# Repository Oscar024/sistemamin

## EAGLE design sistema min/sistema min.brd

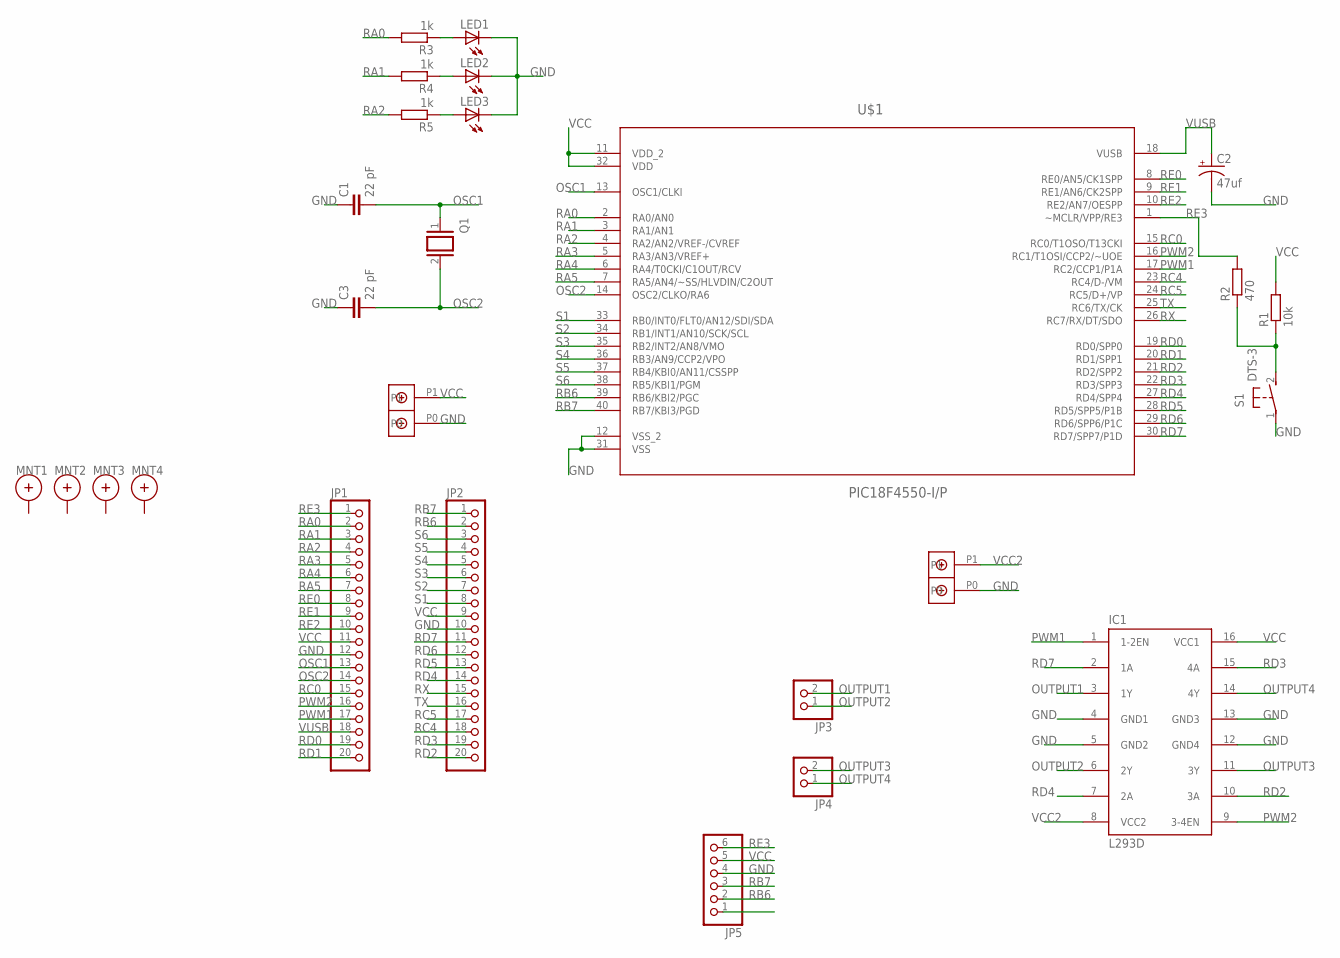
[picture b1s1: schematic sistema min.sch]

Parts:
C1, C3: 22 pF; C050-025X075
C2: 47uf; E5-10,5
IC1: L293D; DIL16
JP1, JP2: PINHD-1X20; 1X20
JP3, JP4: PINHD-1X2; 1X02
JP5: PINHD-1X6; 1X06
LED1, LED2, LED3: LED3MM
MNT1, MNT2, MNT3, MNT4: HOLE_MNT_0.135; HOLE_MNT_#5-40
Q1: XTAL/S; QS
R1: 10k; 0204/7
R2: 470; 0204/7
R3, R4, R5: 1k; 0204/7
S1: DTS-3
U$1: PIC18F4550-I/P; DIP254P1524X635-40
U$2, U$3: DBCONN-1X2

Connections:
GND: C1.1, C2.-, C3.1, IC1.4 (GND1), IC1.5 (GND2), IC1.12 (GND4), IC1.13 (GND3), JP1.12, JP2.10, JP5.4, LED1.K (C), LED2.K (C), LED3.K (C), S1.1, U$1.12 (VSS_2), U$1.31 (VSS), U$2.P0, U$3.P0
unnamed: R1.1, R2.1, S1.2
unnamed: LED1.A, R3.1
unnamed: LED2.A, R4.1
unnamed: LED3.A, R5.1
OSC1: C1.2, JP1.13, Q1.1, U$1.13 (OSC1/CLKI)
OSC2: C3.2, JP1.14, Q1.2, U$1.14 (OSC2/CLKO/RA6)
OUTPUT1: IC1.3 (1Y), JP3.2
OUTPUT2: IC1.6 (2Y), JP3.1
OUTPUT3: IC1.11 (3Y), JP4.2
OUTPUT4: IC1.14 (4Y), JP4.1
PWM1: IC1.1 (1-2EN), JP1.17, U$1.17 (RC2/CCP1/P1A)
PWM2: IC1.9 (3-4EN), JP1.16, U$1.16 (RC1/T1OSI/CCP2/~UOE)
RA0: JP1.2, R3.2, U$1.2 (RA0/AN0)
RA1: JP1.3, R4.2, U$1.3 (RA1/AN1)
RA2: JP1.4, R5.2, U$1.4 (RA2/AN2/VREF-/CVREF)
RA3: JP1.5, U$1.5 (RA3/AN3/VREF+)
RA4: JP1.6, U$1.6 (RA4/T0CKI/C1OUT/RCV)
RA5: JP1.7, U$1.7 (RA5/AN4/~SS/HLVDIN/C2OUT)
RB6: JP2.2, JP5.2, U$1.39 (RB6/KBI2/PGC)
RB7: JP2.1, JP5.3, U$1.40 (RB7/KBI3/PGD)
RC0: JP1.15, U$1.15 (RC0/T1OSO/T13CKI)
RC4: JP2.18, U$1.23 (RC4/D-/VM)
RC5: JP2.17, U$1.24 (RC5/D+/VP)
RD0: JP1.19, U$1.19 (RD0/SPP0)
RD1: JP1.20, U$1.20 (RD1/SPP1)
RD2: IC1.10 (3A), JP2.20, U$1.21 (RD2/SPP2)
RD3: IC1.15 (4A), JP2.19, U$1.22 (RD3/SPP3)
RD4: IC1.7 (2A), JP2.14, U$1.27 (RD4/SPP4)
RD5: JP2.13, U$1.28 (RD5/SPP5/P1B)
RD6: JP2.12, U$1.29 (RD6/SPP6/P1C)
RD7: IC1.2 (1A), JP2.11, U$1.30 (RD7/SPP7/P1D)
RE0: JP1.8, U$1.8 (RE0/AN5/CK1SPP)
RE1: JP1.9, U$1.9 (RE1/AN6/CK2SPP)
RE2: JP1.10, U$1.10 (RE2/AN7/OESPP)
RE3: JP1.1, JP5.6, R2.2, U$1.1 (~MCLR/VPP/RE3)
RX: JP2.15, U$1.26 (RC7/RX/DT/SDO)
S1: JP2.8, U$1.33 (RB0/INT0/FLT0/AN12/SDI/SDA)
S2: JP2.7, U$1.34 (RB1/INT1/AN10/SCK/SCL)
S3: JP2.6, U$1.35 (RB2/INT2/AN8/VMO)
S4: JP2.5, U$1.36 (RB3/AN9/CCP2/VPO)
S5: JP2.4, U$1.37 (RB4/KBI0/AN11/CSSPP)
S6: JP2.3, U$1.38 (RB5/KBI1/PGM)
TX: JP2.16, U$1.25 (RC6/TX/CK)
VCC: IC1.16 (VCC1), JP1.11, JP2.9, JP5.5, R1.2, U$1.11 (VDD_2), U$1.32 (VDD), U$2.P1
VCC2: IC1.8 (VCC2), U$3.P1
VUSB: C2.+, JP1.18, U$1.18 (VUSB)

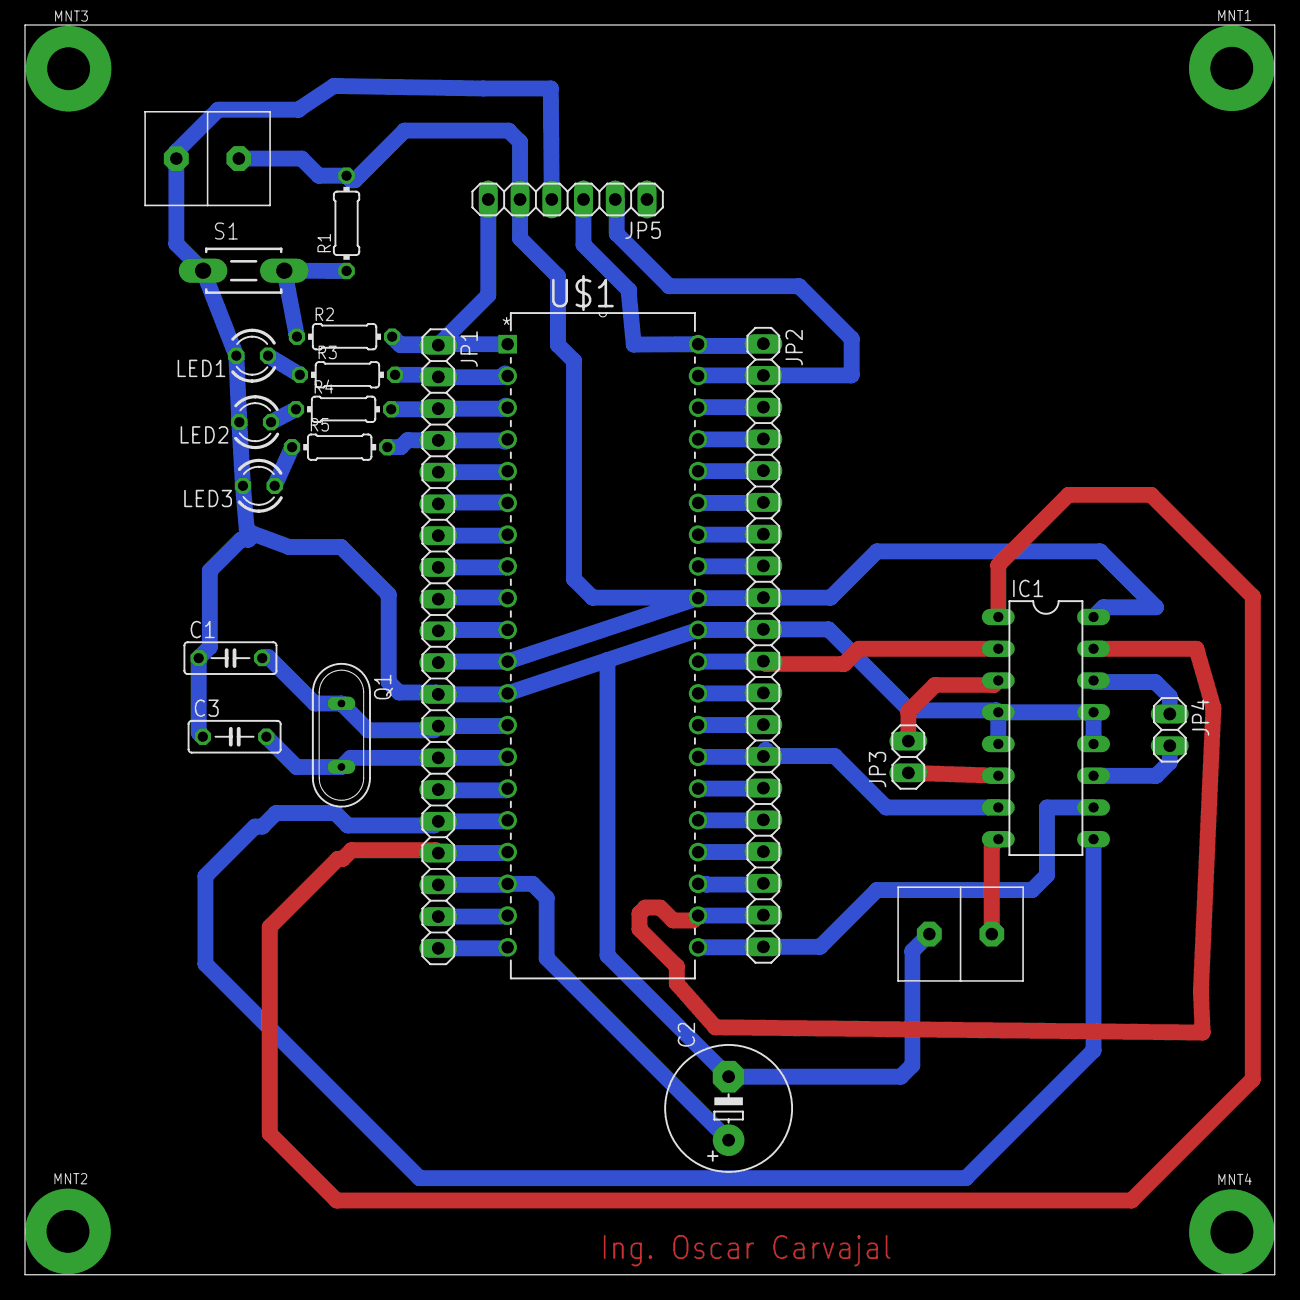
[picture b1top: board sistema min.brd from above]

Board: 2 copper layers, 100.0 x 100.0 mm, 26 parts (0 on the bottom side), 47 nets.
